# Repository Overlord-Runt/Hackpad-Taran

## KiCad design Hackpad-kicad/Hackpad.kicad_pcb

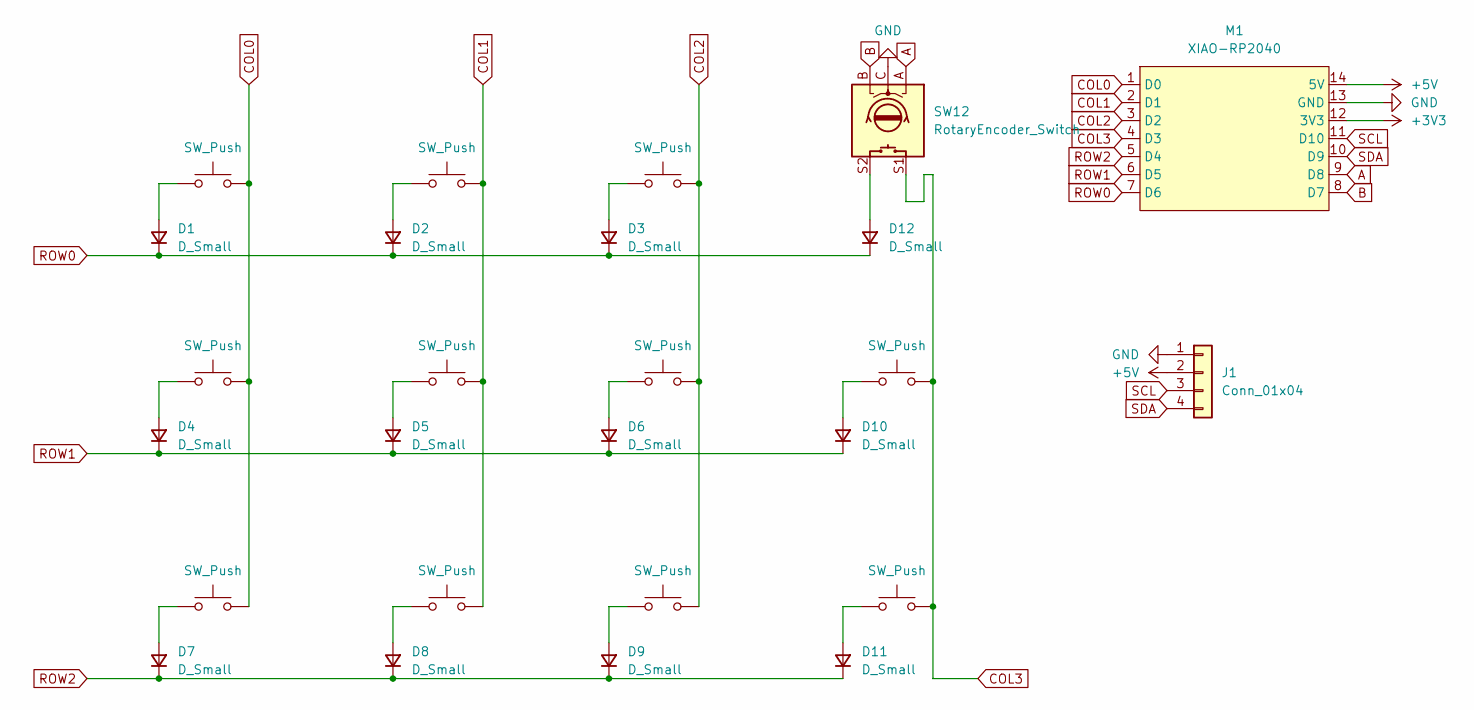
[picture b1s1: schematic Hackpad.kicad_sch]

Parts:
D1, D2, D3, D4, D5, D6, D7, D8, D9, D10, D11, D12: D_Small; DIODE-1N4148
J1: Conn_01x04; SSD1306-0.91-OLED-4pin-128x32
M1: XIAO-RP2040
SW1, SW2, SW3, SW4, SW5, SW6, SW7, SW8, SW9, SW10, SW11: SW_Push; SW_Cherry_MX_1.00u_PCB
SW12: RotaryEncoder_Switch; RotaryEncoder_Alps_EC11E-Switch_Vertical_H20mm

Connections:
+3V3: M1.12 (3V3)
+5V: J1.2, M1.14 (5V)
A: M1.9 (D8), SW12.A
B: M1.8 (D7), SW12.B
COL0: M1.1 (D0), SW1.2, SW4.2, SW7.2
COL1: M1.2 (D1), SW2.2, SW5.2, SW8.2
COL2: M1.3 (D2), SW3.2, SW6.2, SW9.2
COL3: M1.4 (D3), SW10.2, SW11.2, SW12.S1
GND: J1.1, M1.13 (GND), SW12.C
unnamed: D1.A, SW1.1
unnamed: D2.A, SW2.1
unnamed: D3.A, SW3.1
unnamed: D4.A, SW4.1
unnamed: D5.A, SW5.1
unnamed: D6.A, SW6.1
unnamed: D7.A, SW7.1
unnamed: D8.A, SW8.1
unnamed: D9.A, SW9.1
unnamed: D10.A, SW10.1
unnamed: D11.A, SW11.1
unnamed: D12.A, SW12.S2
ROW0: D1.K, D2.K, D3.K, D12.K, M1.7 (D6)
ROW1: D4.K, D5.K, D6.K, D10.K, M1.6 (D5)
ROW2: D7.K, D8.K, D9.K, D11.K, M1.5 (D4)
SCL: J1.3, M1.11 (D10)
SDA: J1.4, M1.10 (D9)

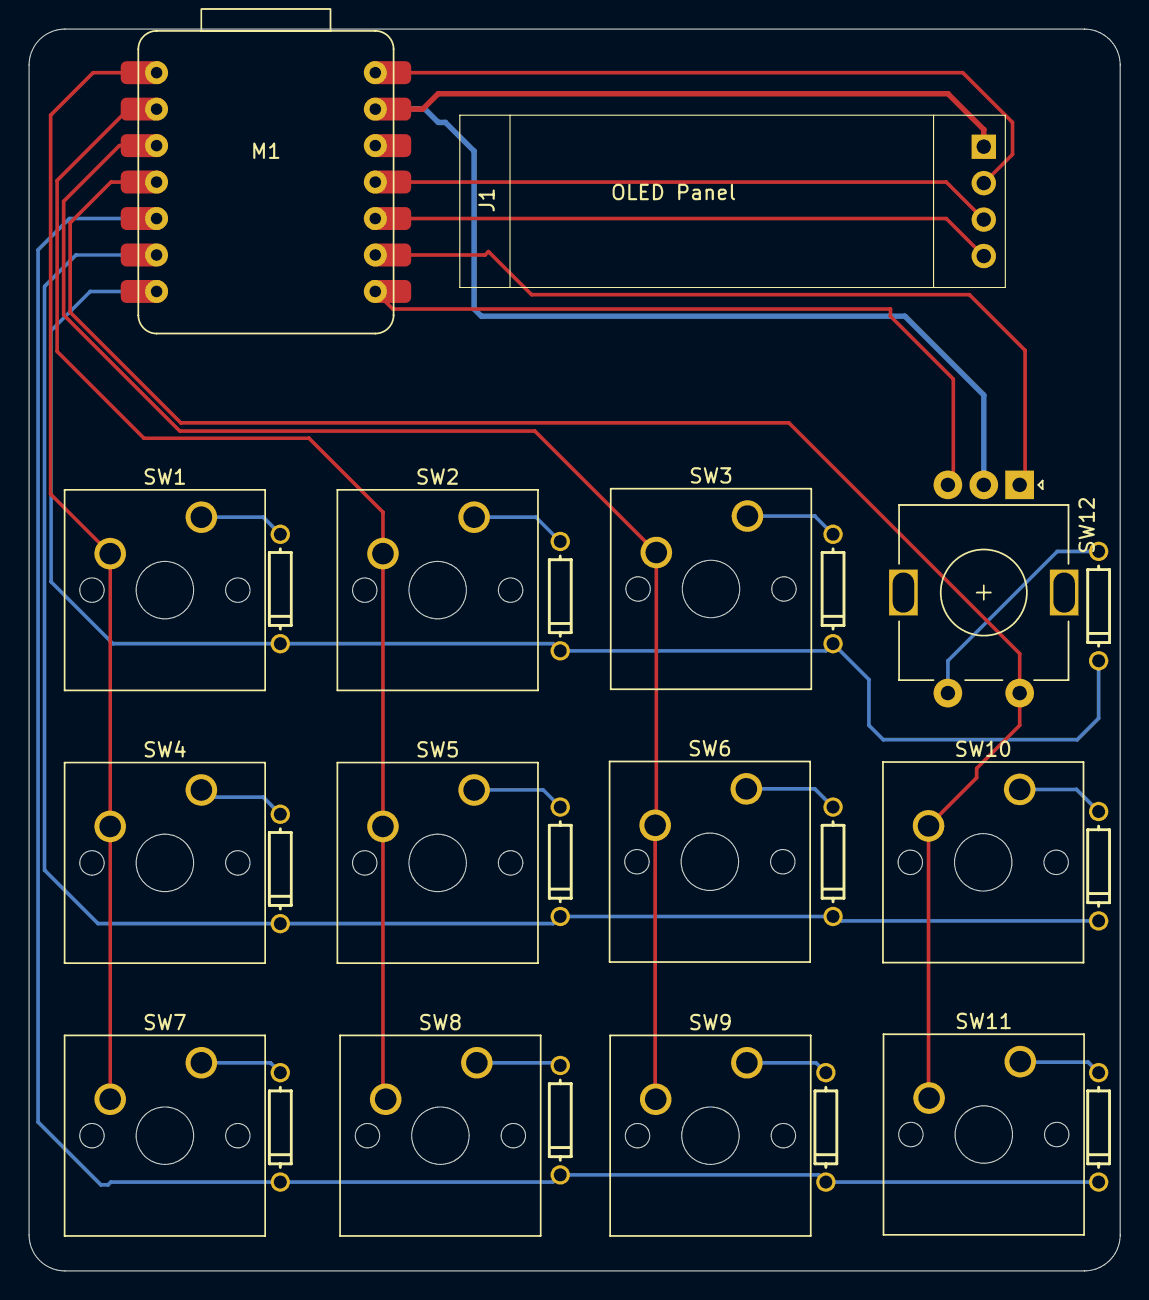
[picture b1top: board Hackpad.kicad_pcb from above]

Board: 2 copper layers, 76.0 x 86.5 mm, 26 parts (0 on the bottom side), 25 nets.
